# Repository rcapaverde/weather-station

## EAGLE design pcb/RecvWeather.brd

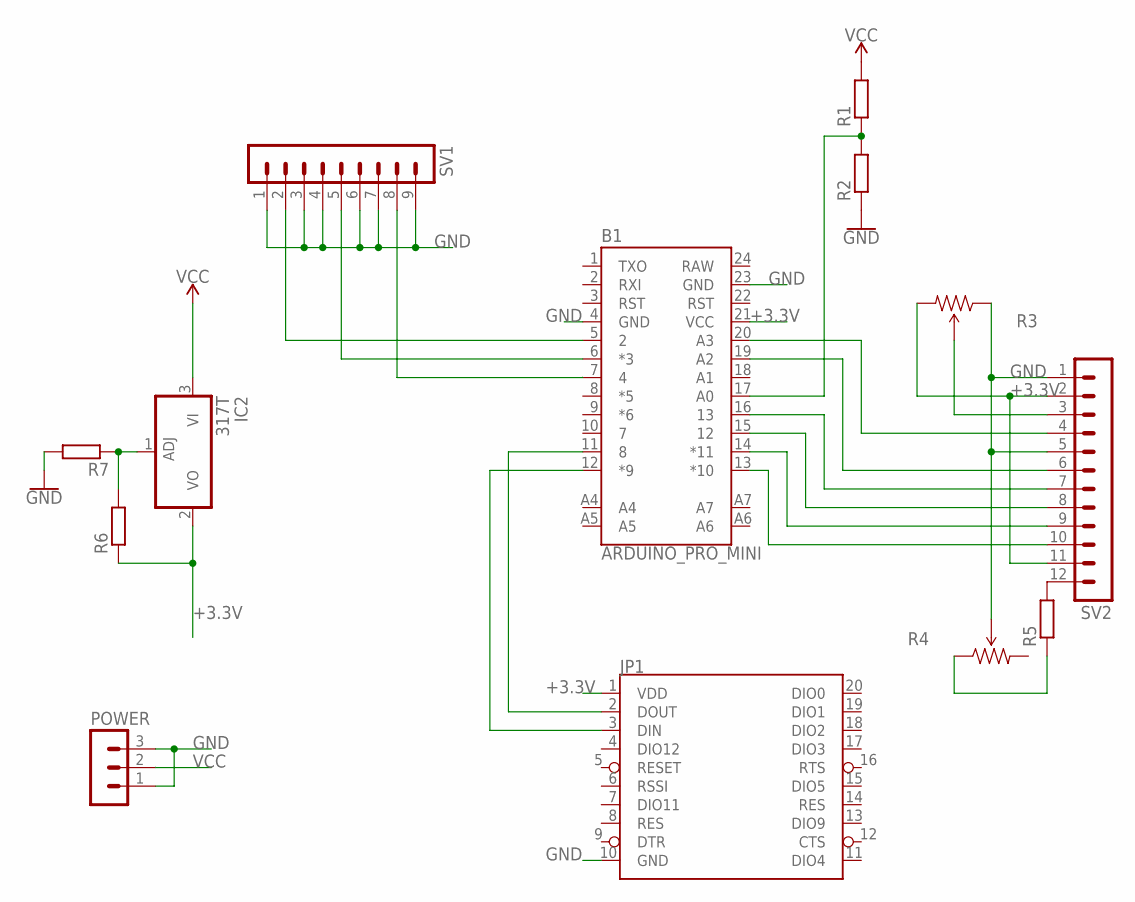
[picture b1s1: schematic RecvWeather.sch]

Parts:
B1: ARDUINO_PRO_MINI
IC2: 317T; TO220H
JP1: XBEE
POWER: MA03-1
R1, R2, R5, R6, R7: R-EU_0309/12; 0309/12
R3, R4: TRIMPOTPTH; TRIM_POT_PTH
SV1: MA09-1
SV2: MA12-1

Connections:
+3.3V: B1.21 (VCC), IC2.2 (VO), JP1.1 (VDD), R3.3 (CW), R6.1, SV2.2, SV2.11
GND: B1.4 (GND), B1.23 (GND), JP1.10 (GND), POWER.1, POWER.3, R2.1, R3.1 (CCW), R4.2 (WIPER), R7.2, SV1.1, SV1.3, SV1.4, SV1.6, SV1.7, SV1.9, SV2.1, SV2.5
unnamed: B1.17 (A0), R1.1, R2.2
unnamed: B1.11 (8), JP1.2 (DOUT)
unnamed: R5.2, SV2.12
unnamed: R4.1 (CCW), R5.1
unnamed: R3.2 (WIPER), SV2.3
unnamed: B1.16 (13), SV2.7
unnamed: B1.12 (*9), JP1.3 (DIN)
unnamed: B1.20 (A3), SV2.4
unnamed: B1.19 (A2), SV2.6
unnamed: B1.5 (2), SV1.2
unnamed: B1.6 (*3), SV1.5
unnamed: B1.7 (4), SV1.8
unnamed: IC2.1 (ADJ), R6.2, R7.1
unnamed: B1.15 (12), SV2.8
unnamed: B1.14 (*11), SV2.9
unnamed: B1.13 (*10), SV2.10
RAW: B1.24 (RAW)
VCC: IC2.3 (VI), POWER.2, R1.2

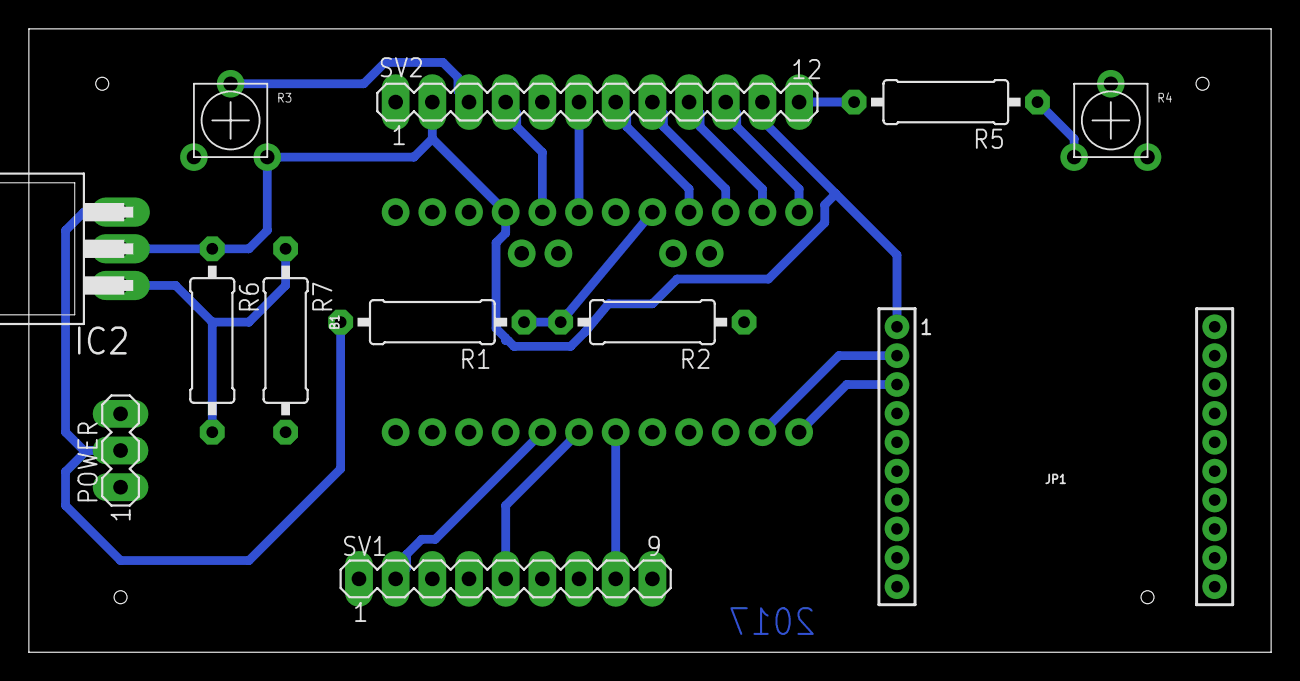
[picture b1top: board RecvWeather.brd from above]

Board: 2 copper layers, 86.0 x 43.2 mm, 13 parts (0 on the bottom side), 19 nets.

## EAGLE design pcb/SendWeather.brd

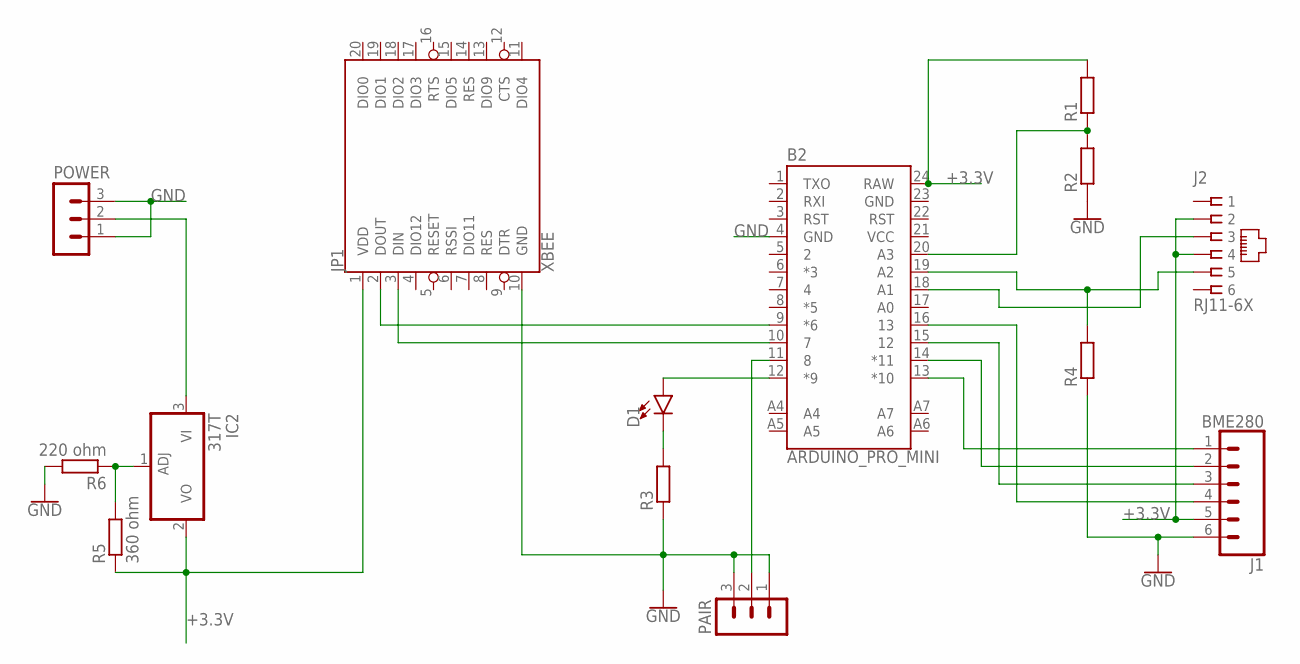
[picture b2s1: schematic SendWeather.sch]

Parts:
B2: ARDUINO_PRO_MINI
D1: LED3MM; LED_3MM
IC2: 317T; TO220H
J1: BME280; 1X06_NO_SILK
J2: RJ11-6X; RJ11-NO_SHIELD
JP1: XBEE
PAIR: MA03-1
POWER: MA03-1
R1, R2, R3, R4: R-EU_0309/12; 0309/12
R5: 360 ohm; 0309/12
R6: 220 ohm; 0309/12

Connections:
+3.3V: B2.24 (RAW), IC2.2 (VO), J1.5, J2.2, J2.4, JP1.1 (VDD), R1.2, R5.1
GND: B2.4 (GND), B2.23 (GND), J1.6, JP1.10 (GND), PAIR.1, PAIR.3, POWER.1, POWER.3, R2.1, R3.1, R4.1, R6.2
unnamed: B2.16 (13), J1.4
unnamed: B2.15 (12), J1.3
unnamed: B2.14 (*11), J1.2
unnamed: B2.12 (*9), D1.A
unnamed: B2.13 (*10), J1.1
unnamed: B2.20 (A3), R1.1, R2.2
unnamed: B2.18 (A1), J2.3
unnamed: D1.K (C), R3.2
unnamed: B2.9 (*6), JP1.2 (DOUT)
unnamed: B2.11 (8), PAIR.2
unnamed: B2.19 (A2), J2.5, R4.2
unnamed: IC2.1 (ADJ), R5.2, R6.1
unnamed: B2.10 (7), JP1.3 (DIN)
VDD: B2.21 (VCC), IC2.3 (VI), POWER.2

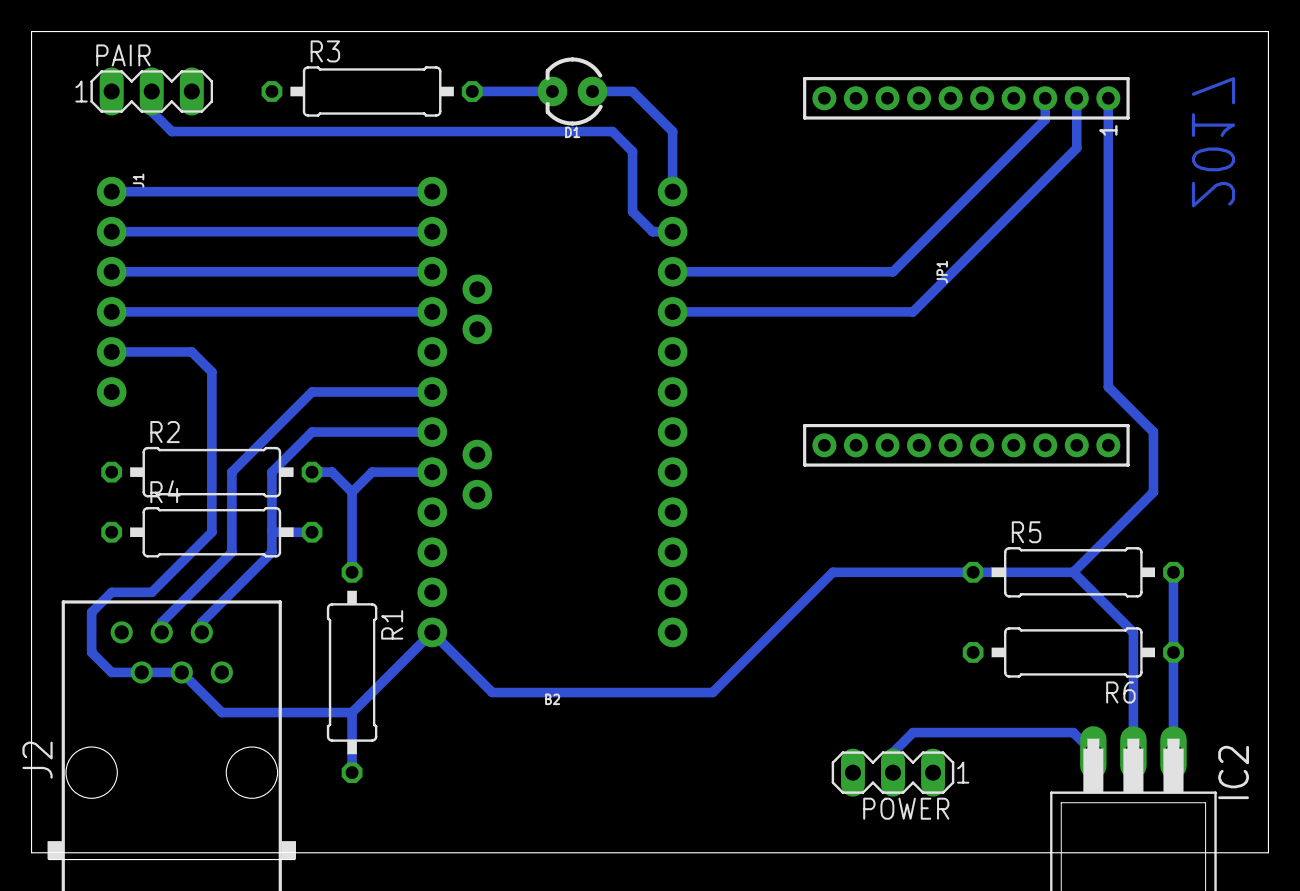
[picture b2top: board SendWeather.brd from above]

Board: 2 copper layers, 78.4 x 52.5 mm, 14 parts (0 on the bottom side), 16 nets.

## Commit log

2018-09-22 no message

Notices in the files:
parts and their libraries:
SparkFun-arduinonano: Licensing: Creative Commons ShareAlike 4.0 International - https://creativecommons.org/licenses/by-sa/4.0
